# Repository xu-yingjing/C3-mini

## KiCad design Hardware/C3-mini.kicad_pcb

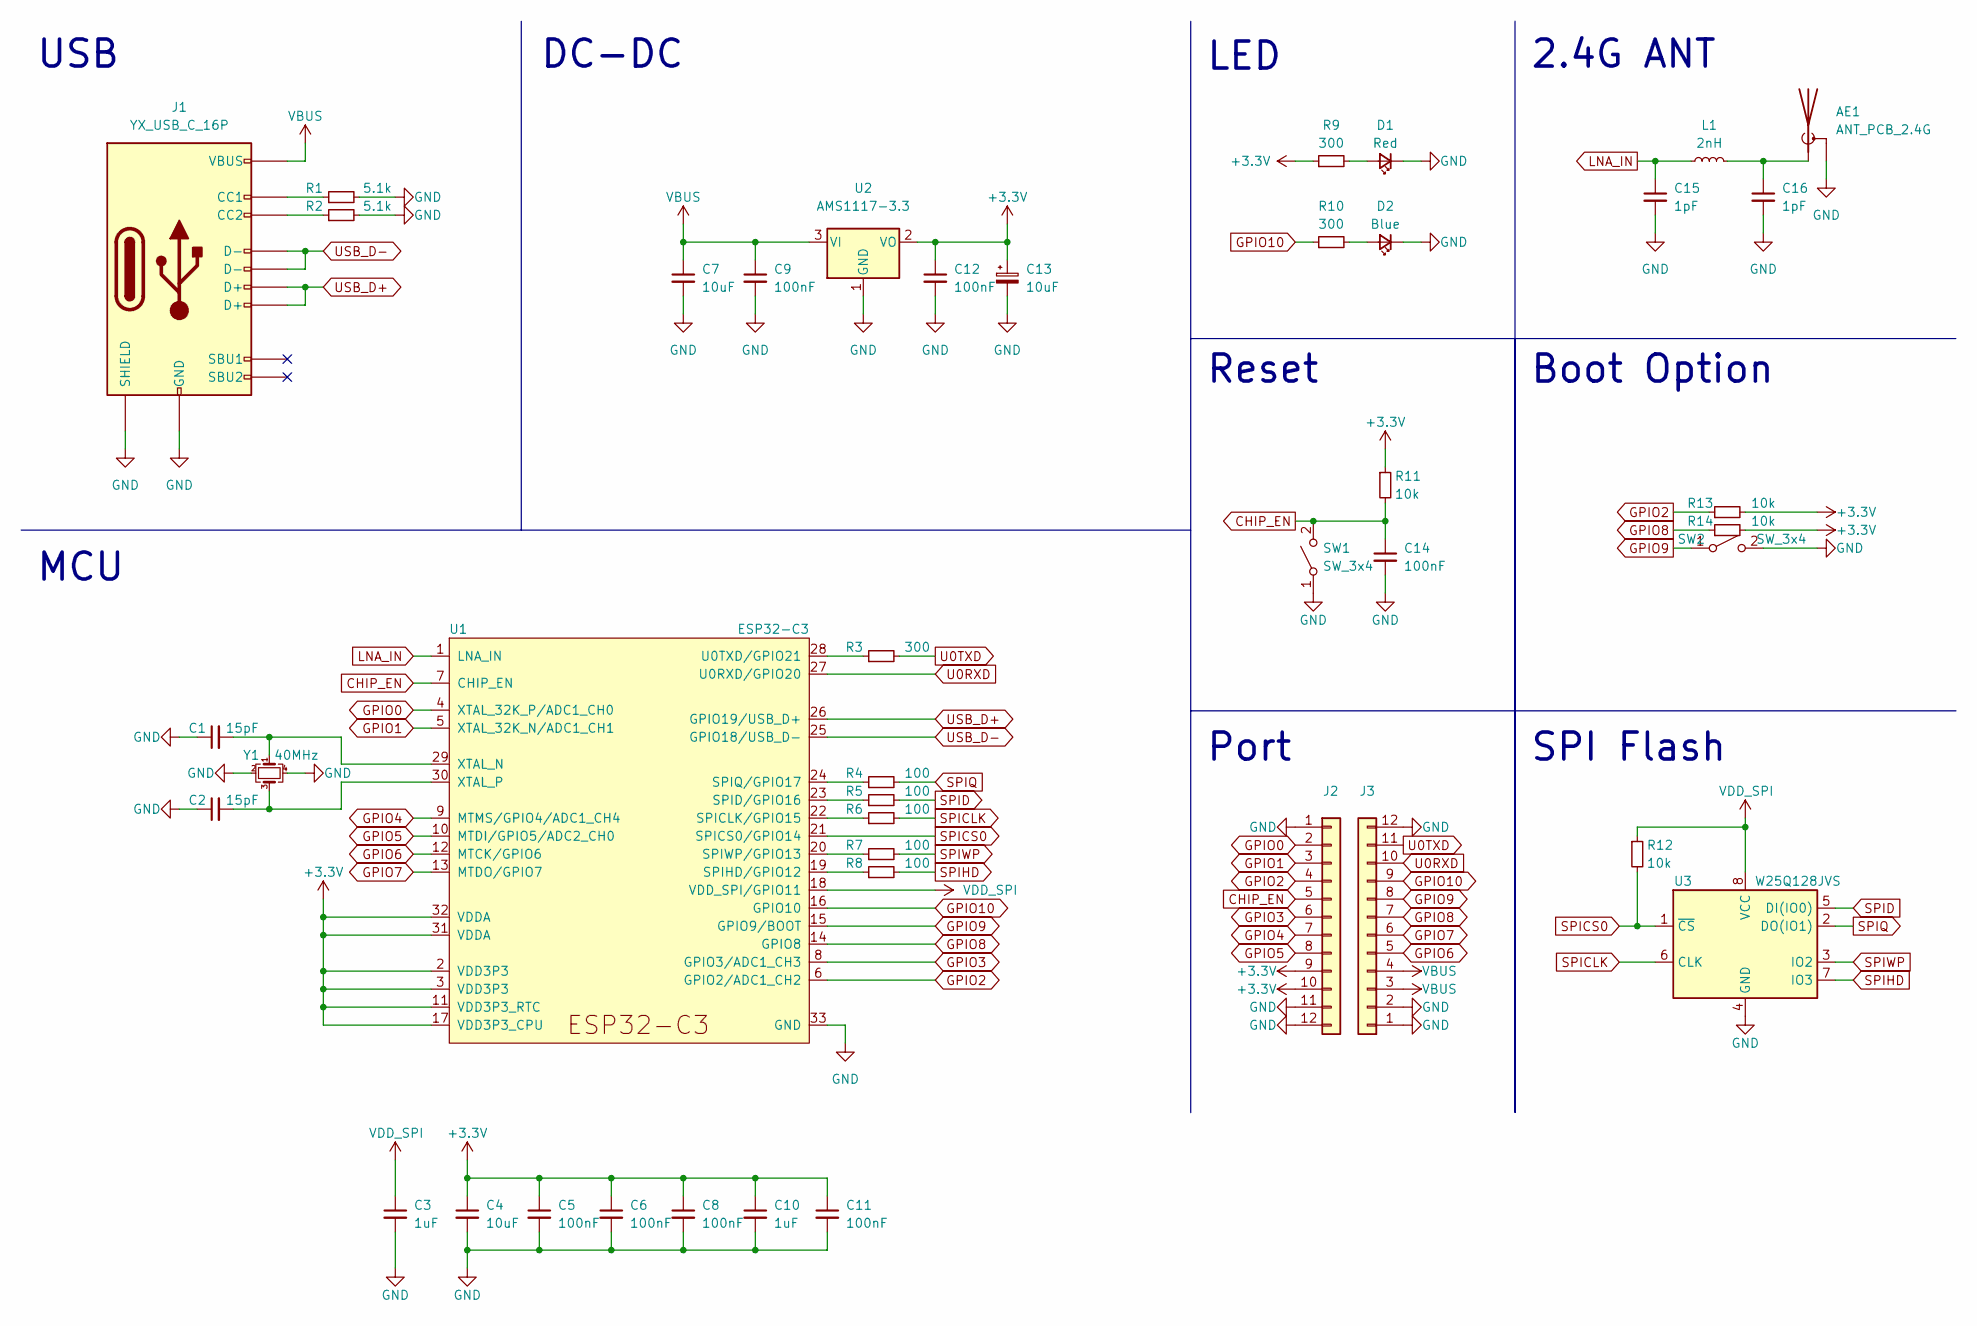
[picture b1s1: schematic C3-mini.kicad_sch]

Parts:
AE1: ANT_PCB_2.4G; Texas_SWRA117D_2.4GHz_Right
C1, C2: 15pF; C_0603_1608Metric
C3, C10: 1uF; C_0603_1608Metric
C4, C7: 10uF; C_0603_1608Metric
C5, C6, C8, C9, C11, C12, C14: 100nF; C_0603_1608Metric
C13: 10uF; CP_EIA-3216-18_Kemet-A
C15, C16: 1pF; C_0603_1608Metric
D1: Red; LED_0603_1608Metric
D2: Blue; LED_0603_1608Metric
J1: YX_USB_C_16P
J2, J3: Conn_01x12; PinHeader_1x12_P2.54mm_Vertical
L1: 2nH; L_0603_1608Metric
R1, R2: 5.1k; R_0603_1608Metric
R3, R9, R10: 300; R_0603_1608Metric
R4, R5, R6, R7, R8: 100; R_0603_1608Metric
R11, R12, R13, R14: 10k; R_0603_1608Metric
SW1, SW2: SW_3x4
U1: ESP32-C3; QFN-32-1EP_5x5mm_P0.5mm_EP3.45x3.45mm
U2: AMS1117-3.3; SOT-223-3_TabPin2
U3: W25Q128JVS; SOIC-8_5.23x5.23mm_P1.27mm
Y1: 40MHz; Crystal_SMD_3225-4Pin_3.2x2.5mm

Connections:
+3.3V: C4.1, C5.1, C6.1, C8.1, C10.1, C11.1, C12.1, C13.1, J2.9, J2.10, R9.1, R11.1, R13.2, R14.2, U1.2 (VDD3P3), U1.3 (VDD3P3), U1.11 (VDD3P3_RTC), U1.17 (VDD3P3_CPU), U1.31 (VDDA), U1.32 (VDDA), U2.2 (VO)
CHIP_EN: C14.1, J2.5, R11.2, SW1.2 (B), U1.7 (CHIP_EN)
GND: AE1.2 (Shield), C1.1, C2.1, C3.2, C4.2, C5.2, C6.2, C7.2, C8.2, C9.2, C10.2, C11.2, C12.2, C13.2, C14.2, C15.2, C16.2, D1.1 (K), D2.1 (K), J1.A1 (GND), J1.A12 (GND), J1.B1 (GND), J1.B12 (GND), J1.S1 (SHIELD), J2.1, J2.11, J2.12, J3.1, J3.2, J3.12, R1.2, R2.2, SW1.1 (A), SW2.2 (B), U1.33 (GND), U2.1 (GND), U3.4 (GND), Y1.2, Y1.4
GPIO0: J2.2, U1.4 (XTAL_32K_P/ADC1_CH0)
GPIO1: J2.3, U1.5 (XTAL_32K_N/ADC1_CH1)
GPIO2: J2.4, R13.1, U1.6 (GPIO2/ADC1_CH2)
GPIO3: J2.6, U1.8 (GPIO3/ADC1_CH3)
GPIO4: J2.7, U1.9 (MTMS/GPIO4/ADC1_CH4)
GPIO5: J2.8, U1.10 (MTDI/GPIO5/ADC2_CH0)
GPIO6: J3.5, U1.12 (MTCK/GPIO6)
GPIO7: J3.6, U1.13 (MTDO/GPIO7)
GPIO8: J3.7, R14.1, U1.14 (GPIO8)
GPIO9: J3.8, SW2.1 (A), U1.15 (GPIO9/BOOT)
GPIO10: J3.9, R10.1, U1.16 (GPIO10)
LNA_IN: C15.1, L1.1, U1.1 (LNA_IN)
unnamed: AE1.1 (A), C16.1, L1.2
unnamed: C1.2, U1.29 (XTAL_N), Y1.1
unnamed: C2.2, U1.30 (XTAL_P), Y1.3
unnamed: D1.2 (A), R9.2
unnamed: D2.2 (A), R10.2
unnamed: J1.A5 (CC1), R1.1
unnamed: J1.B5 (CC2), R2.1
unnamed: R3.1, U1.28 (U0TXD/GPIO21)
unnamed: R4.1, U1.24 (SPIQ/GPIO17)
unnamed: R5.1, U1.23 (SPID/GPIO16)
unnamed: R6.1, U1.22 (SPICLK/GPIO15)
unnamed: R7.1, U1.20 (SPIWP/GPIO13)
unnamed: R8.1, U1.19 (SPIHD/GPIO12)
SPICLK: R6.2, U3.6 (CLK)
SPICS0: R12.2, U1.21 (SPICS0/GPIO14), U3.1 (~CS)
SPID: R5.2, U3.5 (DI(IO0))
SPIHD: R8.2, U3.7 (IO3)
SPIQ: R4.2, U3.2 (DO(IO1))
SPIWP: R7.2, U3.3 (IO2)
U0RXD: J3.10, U1.27 (U0RXD/GPIO20)
U0TXD: J3.11, R3.2
USB_D+: J1.A6 (D+), J1.B6 (D+), U1.26 (GPIO19/USB_D+)
USB_D-: J1.A7 (D-), J1.B7 (D-), U1.25 (GPIO18/USB_D-)
VBUS: C7.1, C9.1, J1.A4 (VBUS), J1.A9 (VBUS), J1.B4 (VBUS), J1.B9 (VBUS), J3.3, J3.4, U2.3 (VI)
VDD_SPI: C3.1, R12.1, U1.18 (VDD_SPI/GPIO11), U3.8 (VCC)

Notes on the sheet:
MCU
Boot Option
2.4G ANT
Reset
SPI Flash
LED
USB
DC-DC
Port

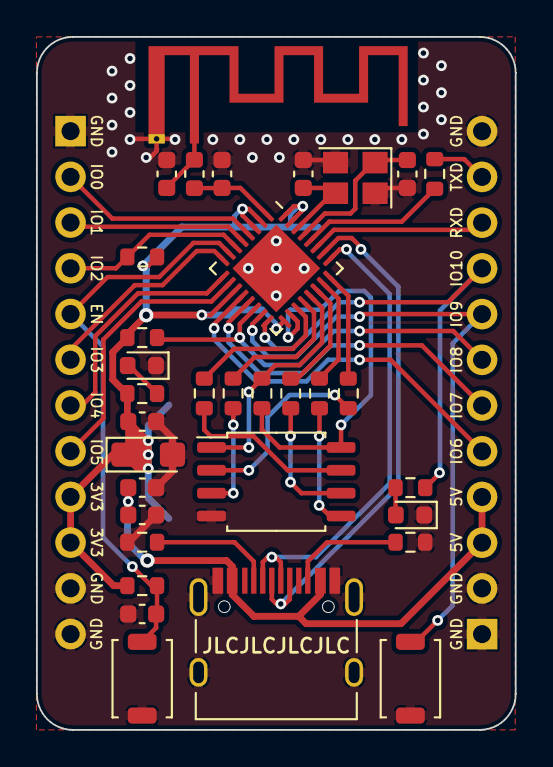
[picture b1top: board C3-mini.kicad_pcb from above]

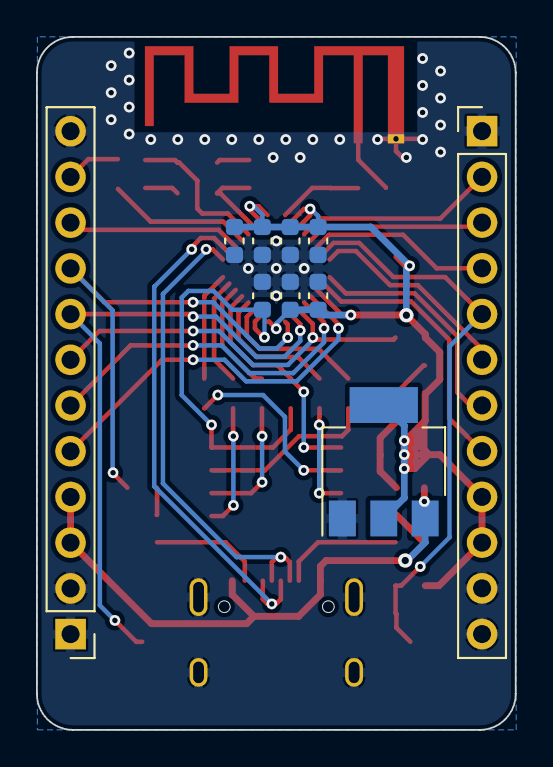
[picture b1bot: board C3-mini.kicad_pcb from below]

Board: 2 copper layers, 26.6 x 38.5 mm, 43 parts (10 on the bottom side), 40 nets.
